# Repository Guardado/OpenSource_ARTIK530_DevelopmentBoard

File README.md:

# OpenSource_ARTIK530_DevelopmentBoard  
An Open Source Development Board for the ARTIK530 SOM  

----

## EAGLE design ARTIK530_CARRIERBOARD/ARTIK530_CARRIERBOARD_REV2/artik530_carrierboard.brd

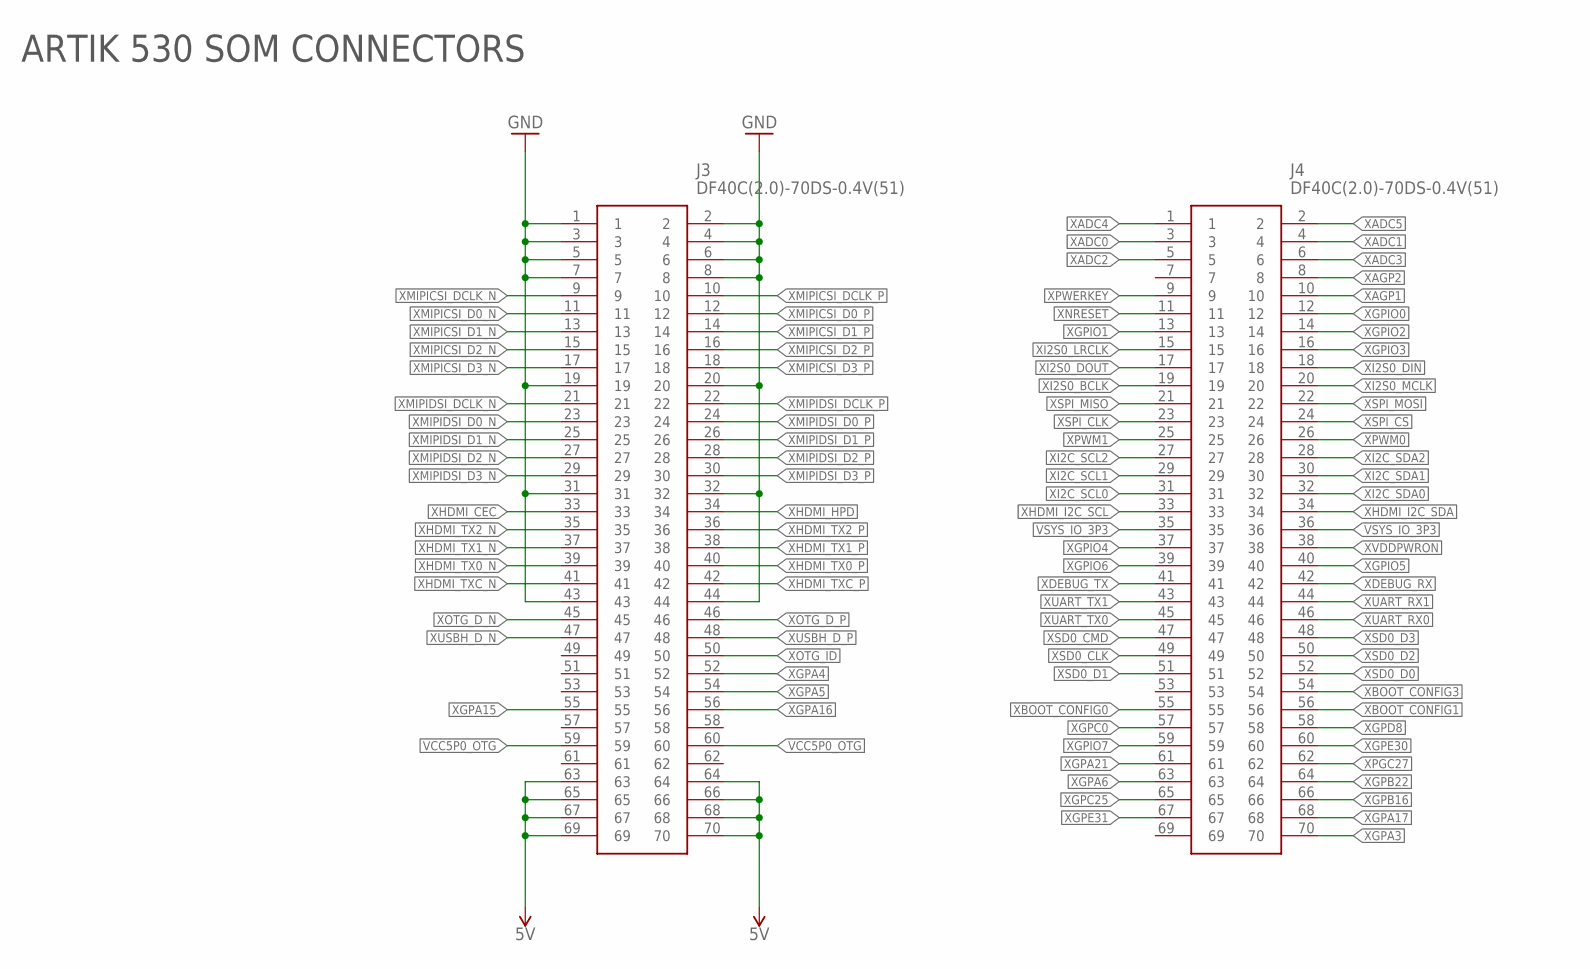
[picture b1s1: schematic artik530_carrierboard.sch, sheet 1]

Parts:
J3, J4: DF40C(2.0)-70DS-0.4V(51)

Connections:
5V: J3.63, J3.64, J3.65, J3.66, J3.67, J3.68, J3.69, J3.70; also elsewhere on the board
GND: J3.1, J3.2, J3.3, J3.4, J3.5, J3.6, J3.7, J3.8, J3.19, J3.20, J3.31, J3.32, J3.43, J3.44; also elsewhere on the board
VCC5P0_OTG: J3.59, J3.60; also elsewhere on the board
VSYS_IO_3P3: J4.35, J4.36; also elsewhere on the board
XADC0: J4.3; also elsewhere on the board
XADC1: J4.4; also elsewhere on the board
XADC2: J4.5; also elsewhere on the board
XADC3: J4.6; also elsewhere on the board
XADC4: J4.1; also elsewhere on the board
XADC5: J4.2; also elsewhere on the board
XAGP1: J4.10
XAGP2: J4.8
XBOOT_CONFIG0: J4.55; also elsewhere on the board
XBOOT_CONFIG1: J4.56; also elsewhere on the board
XBOOT_CONFIG3: J4.54; also elsewhere on the board
XDEBUG_RX: J4.42; also elsewhere on the board
XDEBUG_TX: J4.41; also elsewhere on the board
XGPA3: J4.70
XGPA4: J3.52
XGPA5: J3.54
XGPA6: J4.63
XGPA15: J3.55; also elsewhere on the board
XGPA16: J3.56; also elsewhere on the board
XGPA17: J4.68
XGPA21: J4.61; also elsewhere on the board
XGPB16: J4.66
XGPB22: J4.64
XGPC0: J4.57
XGPC25: J4.65
XGPD8: J4.58; also elsewhere on the board
XGPE30: J4.60
XGPE31: J4.67
XGPIO0: J4.12; also elsewhere on the board
XGPIO1: J4.13; also elsewhere on the board
XGPIO2: J4.14; also elsewhere on the board
XGPIO3: J4.16; also elsewhere on the board
XGPIO4: J4.37; also elsewhere on the board
XGPIO5: J4.40; also elsewhere on the board
XGPIO6: J4.39; also elsewhere on the board
XGPIO7: J4.59; also elsewhere on the board
XHDMI_CEC: J3.33; also elsewhere on the board
XHDMI_HPD: J3.34; also elsewhere on the board
XHDMI_I2C_SCL: J4.33; also elsewhere on the board
XHDMI_I2C_SDA: J4.34; also elsewhere on the board
XHDMI_TX0_N: J3.39; also elsewhere on the board
XHDMI_TX0_P: J3.40; also elsewhere on the board
XHDMI_TX1_N: J3.37; also elsewhere on the board
XHDMI_TX1_P: J3.38; also elsewhere on the board
XHDMI_TX2_N: J3.35; also elsewhere on the board
XHDMI_TX2_P: J3.36; also elsewhere on the board
XHDMI_TXC_N: J3.41; also elsewhere on the board
XHDMI_TXC_P: J3.42; also elsewhere on the board
XI2C_SCL0: J4.31; also elsewhere on the board
XI2C_SCL1: J4.29; also elsewhere on the board
XI2C_SCL2: J4.27; also elsewhere on the board
XI2C_SDA0: J4.32; also elsewhere on the board
XI2C_SDA1: J4.30; also elsewhere on the board
XI2C_SDA2: J4.28; also elsewhere on the board
XI2S0_BCLK: J4.19; also elsewhere on the board
XI2S0_DIN: J4.18; also elsewhere on the board
XI2S0_DOUT: J4.17; also elsewhere on the board
XI2S0_LRCLK: J4.15; also elsewhere on the board
XI2S0_MCLK: J4.20; also elsewhere on the board
XMIPICSI_D0_N: J3.11
XMIPICSI_D0_P: J3.12
XMIPICSI_D1_N: J3.13
XMIPICSI_D1_P: J3.14
XMIPICSI_D2_N: J3.15
XMIPICSI_D2_P: J3.16
XMIPICSI_D3_N: J3.17
XMIPICSI_D3_P: J3.18
XMIPICSI_DCLK_N: J3.9
XMIPICSI_DCLK_P: J3.10
XMIPIDSI_D0_N: J3.23
XMIPIDSI_D0_P: J3.24
XMIPIDSI_D1_N: J3.25
XMIPIDSI_D1_P: J3.26
XMIPIDSI_D2_N: J3.27
XMIPIDSI_D2_P: J3.28
XMIPIDSI_D3_N: J3.29
XMIPIDSI_D3_P: J3.30
XMIPIDSI_DCLK_N: J3.21
XMIPIDSI_DCLK_P: J3.22
XNRESET: J4.11; also elsewhere on the board
XOTG_D_N: J3.45; also elsewhere on the board
XOTG_D_P: J3.46; also elsewhere on the board
XOTG_ID: J3.50; also elsewhere on the board
XPGC27: J4.62
XPWERKEY: J4.9; also elsewhere on the board
XPWM0: J4.26; also elsewhere on the board
XPWM1: J4.25; also elsewhere on the board
XSD0_CLK: J4.49
XSD0_CMD: J4.47
XSD0_D0: J4.52
XSD0_D1: J4.51
XSD0_D2: J4.50
XSD0_D3: J4.48
XSPI_CLK: J4.23; also elsewhere on the board
XSPI_CS: J4.24; also elsewhere on the board
XSPI_MISO: J4.21; also elsewhere on the board
XSPI_MOSI: J4.22; also elsewhere on the board
XUART_RX0: J4.46; also elsewhere on the board
XUART_RX1: J4.44; also elsewhere on the board
XUART_TX0: J4.45; also elsewhere on the board
XUART_TX1: J4.43; also elsewhere on the board
XUSBH_D_N: J3.47; also elsewhere on the board
XUSBH_D_P: J3.48; also elsewhere on the board
XVDDPWRON: J4.38; also elsewhere on the board

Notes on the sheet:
ARTIK 530 SOM CONNECTORS

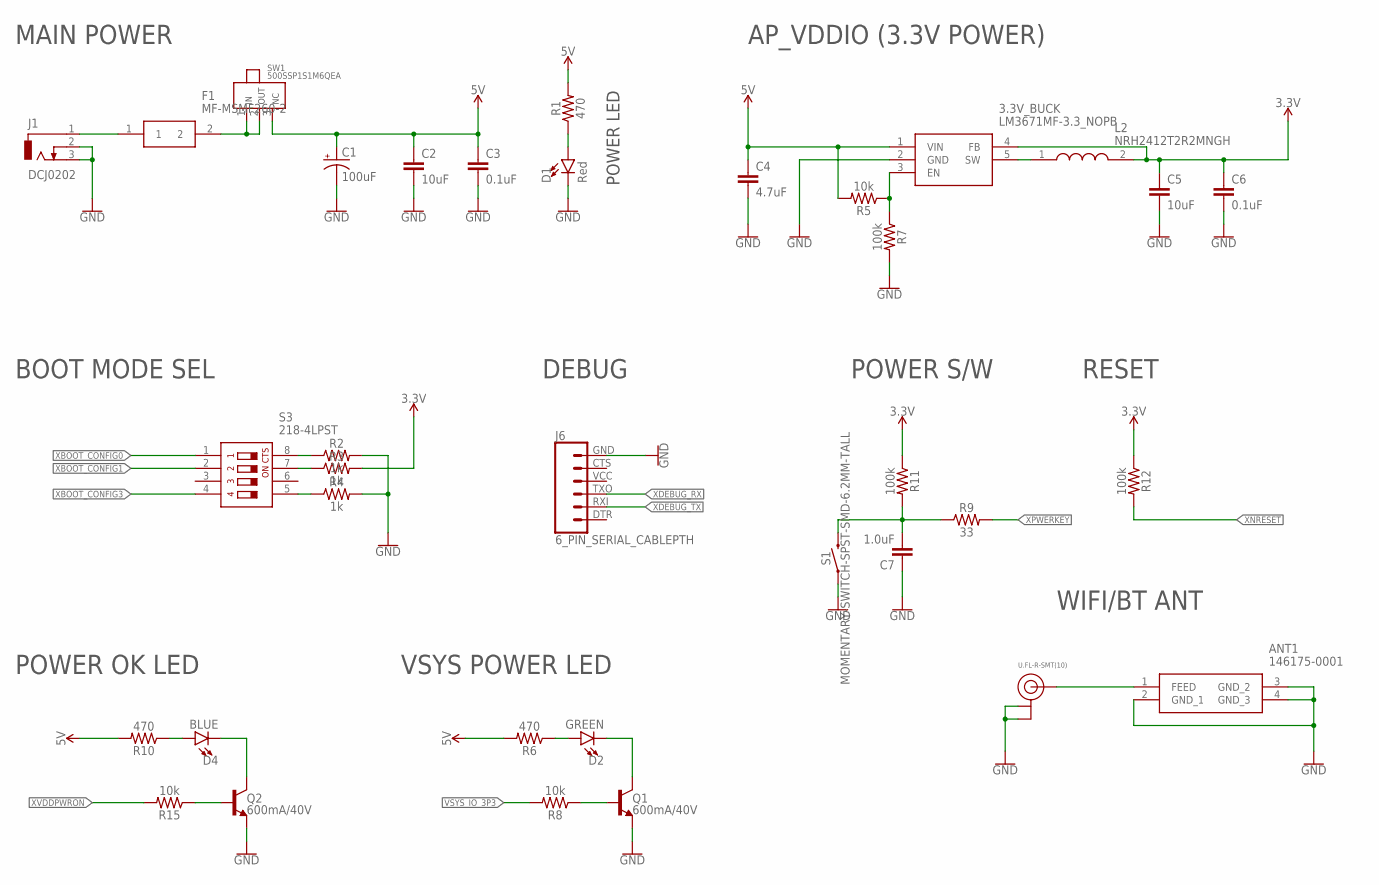
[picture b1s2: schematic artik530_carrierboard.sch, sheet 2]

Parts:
3.3V_BUCK: LM3671MF-3.3_NOPB; SOT95P284X122-5N
ANT1: 146175-0001
C1: 100uF; EIA7343
C2, C5: 10uF; 0603
C3, C6: 0.1uF; 0603
C4: 4.7uF; 0603
C7: 1.0uF; 0603
D1: Red; LED-0603
D2: GREEN; LED-0603
D4: BLUE; LED-0603
F1: MF-MSMF260-2
J1: DCJ0202
J6: 6_PIN_SERIAL_CABLEPTH; FTDI_BASIC
L2: NRH2412T2R2MNGH
Q1, Q2: 600mA/40V; SOT23-3
R1, R6, R10: 470; 0603
R2, R3, R4: 1k; 0603
R5, R8, R15: 10k; 0603
R7, R11, R12: 100k; 0603
R9: 33; 0603
S1: MOMENTARY-SWITCH-SPST-SMD-6.2MM-TALL; TACTILE_SWITCH_SMD_6.2MM_TALL
S3: 218-4LPST; SOIC127P844X265-8N
SW1: 500SSP1S1M6QEA
U$3: U.FL-R-SMT(10)

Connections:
3.3V: 3.3V_BUCK.4 (FB), C5.1, C6.1, L2.2, R3.2, R11.1, R12.1; also elsewhere on the board
5V: 3.3V_BUCK.1 (VIN), C1.A (+), C2.1, C3.1, C4.1, R1.2, R5.2, R6.2, R10.2, SW1.3 (NC); also elsewhere on the board
GND: 3.3V_BUCK.2 (GND), ANT1.2 (GND_1), ANT1.3 (GND_2), ANT1.4 (GND_3), C1.C (-), C2.2, C3.2, C4.2, C5.2, C6.2, C7.1, D1.C, J1.2, J1.3, J6.GND (6), Q1.2 (E), Q2.2 (E), R2.2, R4.2, R7.2, S1.A2 (1), U$3.1 (GND1), U$3.2 (GND2); also elsewhere on the board
unnamed: F1.1, J1.1
unnamed: F1.2, SW1.1 (IN), SW1.2 (OUT)
unnamed: 3.3V_BUCK.5 (SW), L2.1
unnamed: D1.A, R1.1
unnamed: R2.1, S3.8
unnamed: R3.1, S3.7
unnamed: R4.1, S3.5
unnamed: D2.A, R6.1
unnamed: 3.3V_BUCK.3 (EN), R5.1, R7.1
unnamed: D2.C, Q1.3 (C)
unnamed: Q1.1 (B), R8.1
unnamed: C7.2, R9.1, R11.2, S1.B2 (2)
unnamed: D4.A, R10.1
unnamed: D4.C, Q2.3 (C)
unnamed: Q2.1 (B), R15.1
unnamed: ANT1.1 (FEED), U$3.3 (SIG)
VSYS_IO_3P3: R8.2; also elsewhere on the board
XBOOT_CONFIG0: S3.1; also elsewhere on the board
XBOOT_CONFIG1: S3.2; also elsewhere on the board
XBOOT_CONFIG3: S3.4; also elsewhere on the board
XDEBUG_RX: J6.TXO (3); also elsewhere on the board
XDEBUG_TX: J6.RXI (2); also elsewhere on the board
XNRESET: R12.2; also elsewhere on the board
XPWERKEY: R9.2; also elsewhere on the board
XVDDPWRON: R15.2; also elsewhere on the board

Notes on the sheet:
MAIN POWER
POWER LED
BOOT MODE SEL
AP_VDDIO (3.3V POWER)
VSYS POWER LED
POWER S/W
RESET
DEBUG
WIFI/BT ANT
POWER OK LED

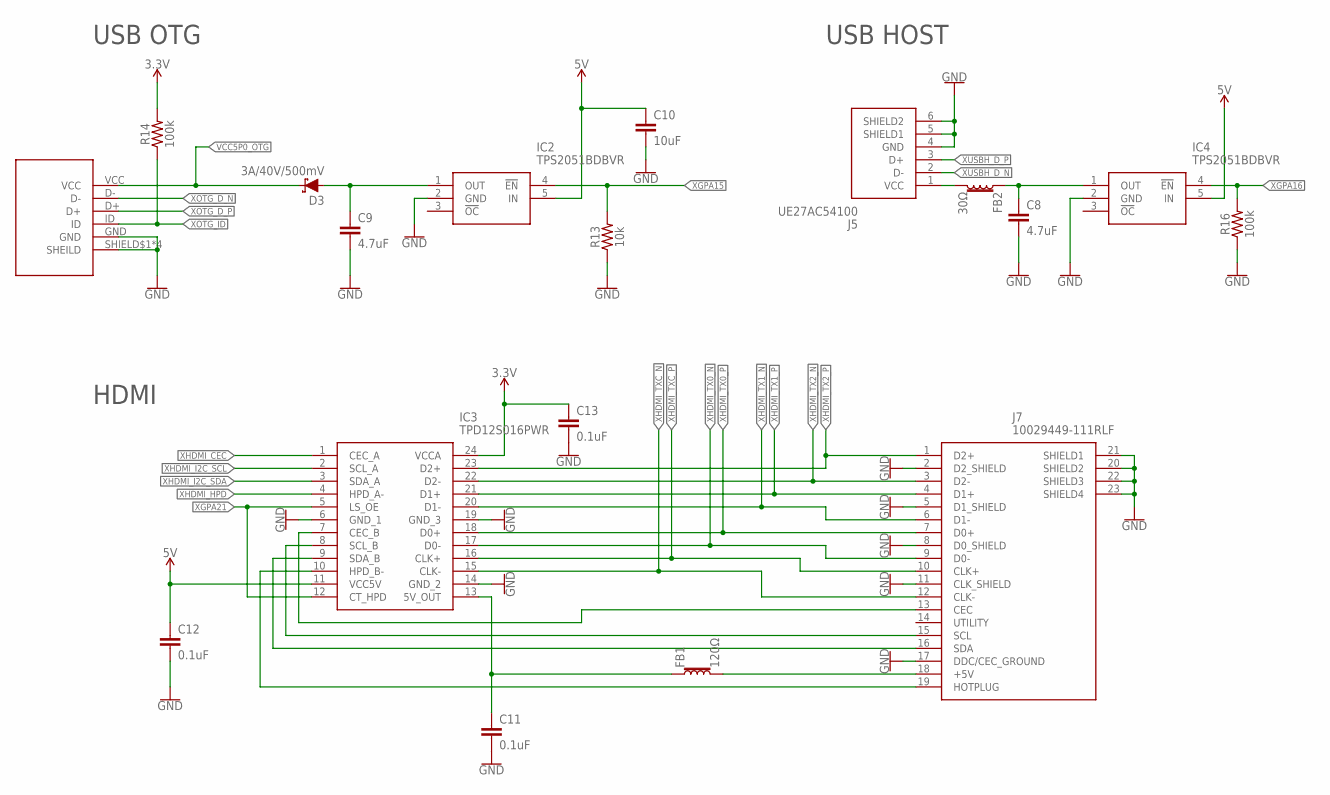
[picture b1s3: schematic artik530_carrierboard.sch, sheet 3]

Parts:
C8, C9: 4.7uF; 0603
C10: 10uF; 0603
C11, C12, C13: 0.1uF; 0603
D3: 3A/40V/500mV; SMA-DIODE
FB1: 120Ω; 0603
FB2: 30Ω; 0603
IC2, IC4: TPS2051BDBVR; SOT95P280X145-5N
IC3: TPD12S016PWR; SOP65P640X120-24N
J2: 10118193-0001LF
J5: UE27AC54100
J7: 10029449-111RLF; 10029449-111RLF_1
R13: 10k; 0603
R14, R16: 100k; 0603

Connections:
3.3V: C13.1, IC3.24 (VCCA), R14.2; also elsewhere on the board
5V: C10.1, C12.1, IC2.5 (IN), IC3.11 (VCC5V), IC4.5 (IN); also elsewhere on the board
GND: C8.2, C9.2, C10.2, C11.2, C12.2, C13.2, IC2.2 (GND), IC3.6 (GND_1), IC3.14 (GND_2), IC3.19 (GND_3), IC4.2 (GND), J2.GND, J2.SHIELD$1 (SHEILD), J2.SHIELD$2 (SHEILD), J2.SHIELD$3 (SHEILD), J2.SHIELD$4 (SHEILD), J5.4 (GND), J5.5 (SHIELD1), J5.6 (SHIELD2), J7.2 (D2_SHIELD), J7.5 (D1_SHIELD), J7.8 (D0_SHIELD), J7.11 (CLK_SHIELD), J7.17 (DDC/CEC_GROUND), J7.20 (SHIELD2), J7.21 (SHIELD1), J7.22 (SHIELD3), J7.23 (SHIELD4), R13.1, R16.1; also elsewhere on the board
unnamed: C11.1, FB1.1, IC3.13 (5V_OUT)
unnamed: C9.1, D3.A, IC2.1 (OUT)
unnamed: IC3.7 (CEC_B), J7.13 (CEC)
unnamed: IC3.8 (SCL_B), J7.15 (SCL)
unnamed: IC3.9 (SDA_B), J7.16 (SDA)
unnamed: IC3.10 (HPD_B-), J7.19 (HOTPLUG)
unnamed: FB1.2, J7.18 (+5V)
unnamed: C8.1, FB2.1, IC4.1 (OUT)
unnamed: FB2.2, J5.1 (VCC)
VCC5P0_OTG: D3.C, J2.VCC; also elsewhere on the board
XGPA15: IC2.4 (!EN), R13.2; also elsewhere on the board
XGPA16: IC4.4 (!EN), R16.2; also elsewhere on the board
XGPA21: IC3.5 (LS_OE), IC3.12 (CT_HPD); also elsewhere on the board
XHDMI_CEC: IC3.1 (CEC_A); also elsewhere on the board
XHDMI_HPD: IC3.4 (HPD_A-); also elsewhere on the board
XHDMI_I2C_SCL: IC3.2 (SCL_A); also elsewhere on the board
XHDMI_I2C_SDA: IC3.3 (SDA_A); also elsewhere on the board
XHDMI_TX0_N: IC3.17 (D0-), J7.9 (D0-); also elsewhere on the board
XHDMI_TX0_P: IC3.18 (D0+), J7.7 (D0+); also elsewhere on the board
XHDMI_TX1_N: IC3.20 (D1-), J7.6 (D1-); also elsewhere on the board
XHDMI_TX1_P: IC3.21 (D1+), J7.4 (D1+); also elsewhere on the board
XHDMI_TX2_N: IC3.22 (D2-), J7.3 (D2-); also elsewhere on the board
XHDMI_TX2_P: IC3.23 (D2+), J7.1 (D2+); also elsewhere on the board
XHDMI_TXC_N: IC3.15 (CLK-), J7.12 (CLK-); also elsewhere on the board
XHDMI_TXC_P: IC3.16 (CLK+), J7.10 (CLK+); also elsewhere on the board
XOTG_D_N: J2.D-; also elsewhere on the board
XOTG_D_P: J2.D+; also elsewhere on the board
XOTG_ID: J2.ID, R14.1; also elsewhere on the board
XUSBH_D_N: J5.2 (D-); also elsewhere on the board
XUSBH_D_P: J5.3 (D+); also elsewhere on the board

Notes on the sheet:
USB OTG
HDMI
USB HOST

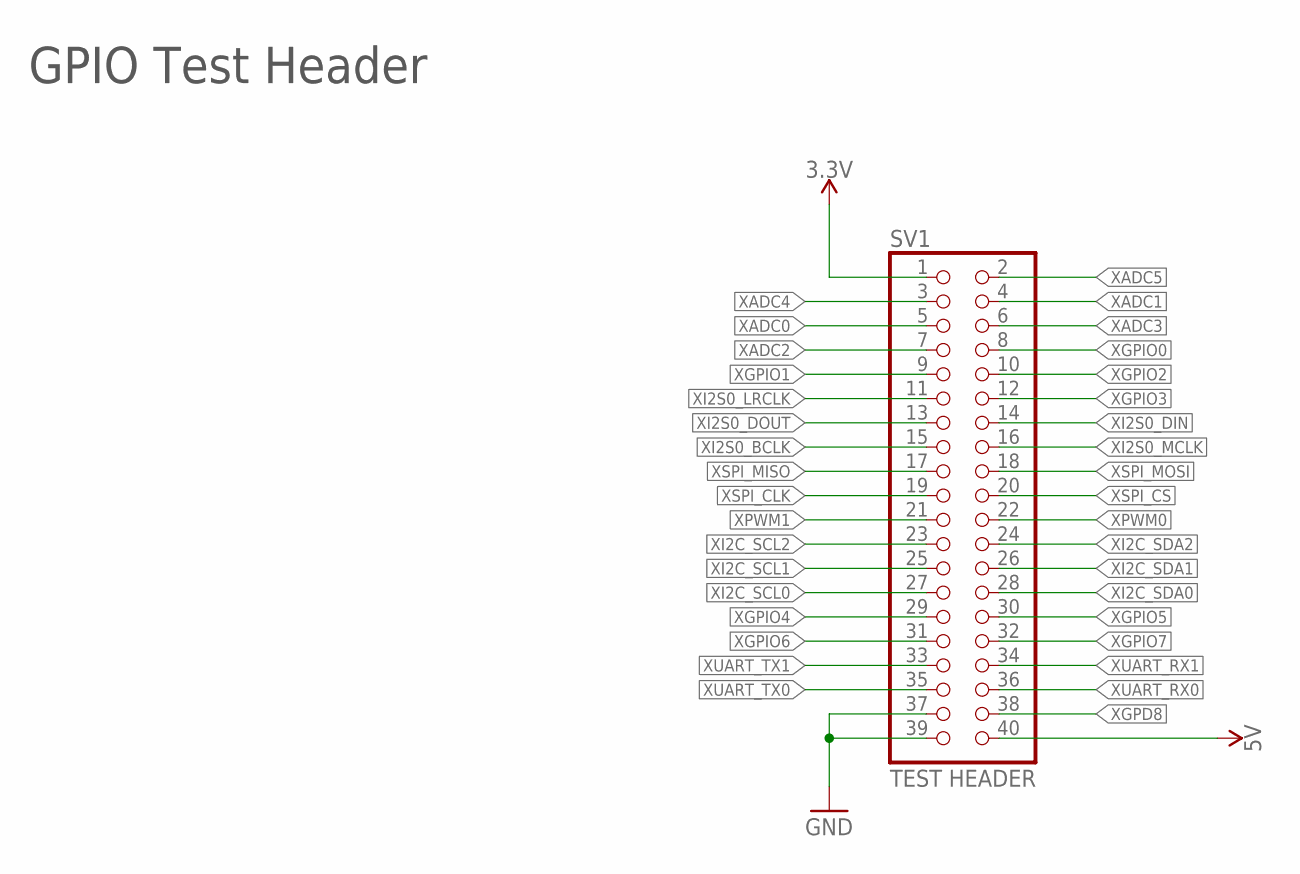
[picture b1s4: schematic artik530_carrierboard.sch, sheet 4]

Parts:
SV1: TEST HEADER; 2X20

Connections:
3.3V: SV1.1; also elsewhere on the board
5V: SV1.40; also elsewhere on the board
GND: SV1.37, SV1.39; also elsewhere on the board
XADC0: SV1.5; also elsewhere on the board
XADC1: SV1.4; also elsewhere on the board
XADC2: SV1.7; also elsewhere on the board
XADC3: SV1.6; also elsewhere on the board
XADC4: SV1.3; also elsewhere on the board
XADC5: SV1.2; also elsewhere on the board
XGPD8: SV1.38; also elsewhere on the board
XGPIO0: SV1.8; also elsewhere on the board
XGPIO1: SV1.9; also elsewhere on the board
XGPIO2: SV1.10; also elsewhere on the board
XGPIO3: SV1.12; also elsewhere on the board
XGPIO4: SV1.29; also elsewhere on the board
XGPIO5: SV1.30; also elsewhere on the board
XGPIO6: SV1.31; also elsewhere on the board
XGPIO7: SV1.32; also elsewhere on the board
XI2C_SCL0: SV1.27; also elsewhere on the board
XI2C_SCL1: SV1.25; also elsewhere on the board
XI2C_SCL2: SV1.23; also elsewhere on the board
XI2C_SDA0: SV1.28; also elsewhere on the board
XI2C_SDA1: SV1.26; also elsewhere on the board
XI2C_SDA2: SV1.24; also elsewhere on the board
XI2S0_BCLK: SV1.15; also elsewhere on the board
XI2S0_DIN: SV1.14; also elsewhere on the board
XI2S0_DOUT: SV1.13; also elsewhere on the board
XI2S0_LRCLK: SV1.11; also elsewhere on the board
XI2S0_MCLK: SV1.16; also elsewhere on the board
XPWM0: SV1.22; also elsewhere on the board
XPWM1: SV1.21; also elsewhere on the board
XSPI_CLK: SV1.19; also elsewhere on the board
XSPI_CS: SV1.20; also elsewhere on the board
XSPI_MISO: SV1.17; also elsewhere on the board
XSPI_MOSI: SV1.18; also elsewhere on the board
XUART_RX0: SV1.36; also elsewhere on the board
XUART_RX1: SV1.34; also elsewhere on the board
XUART_TX0: SV1.35; also elsewhere on the board
XUART_TX1: SV1.33; also elsewhere on the board

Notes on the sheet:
GPIO Test Header

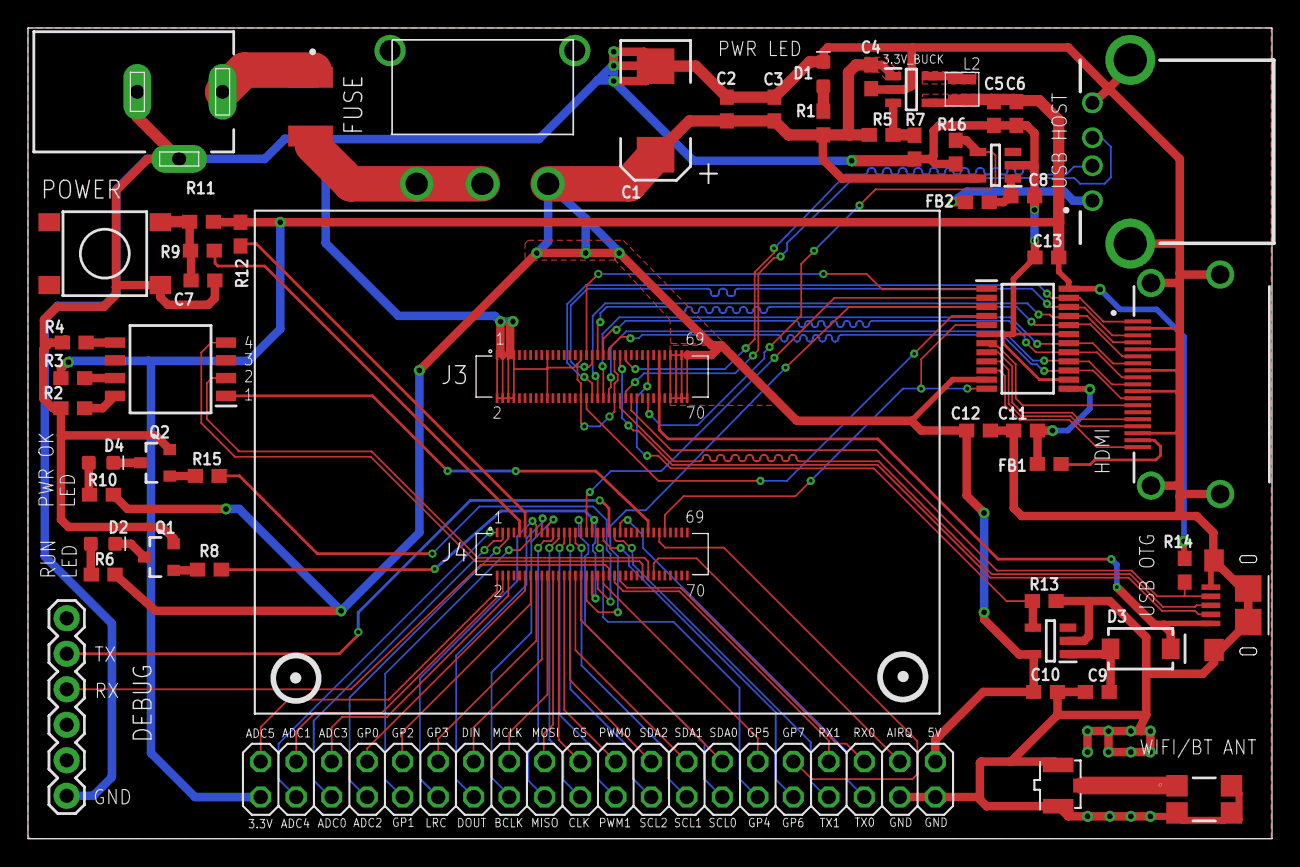
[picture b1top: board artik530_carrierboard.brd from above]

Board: 2 copper layers, 89.0 x 58.0 mm, 56 parts (0 on the bottom side), 94 nets.

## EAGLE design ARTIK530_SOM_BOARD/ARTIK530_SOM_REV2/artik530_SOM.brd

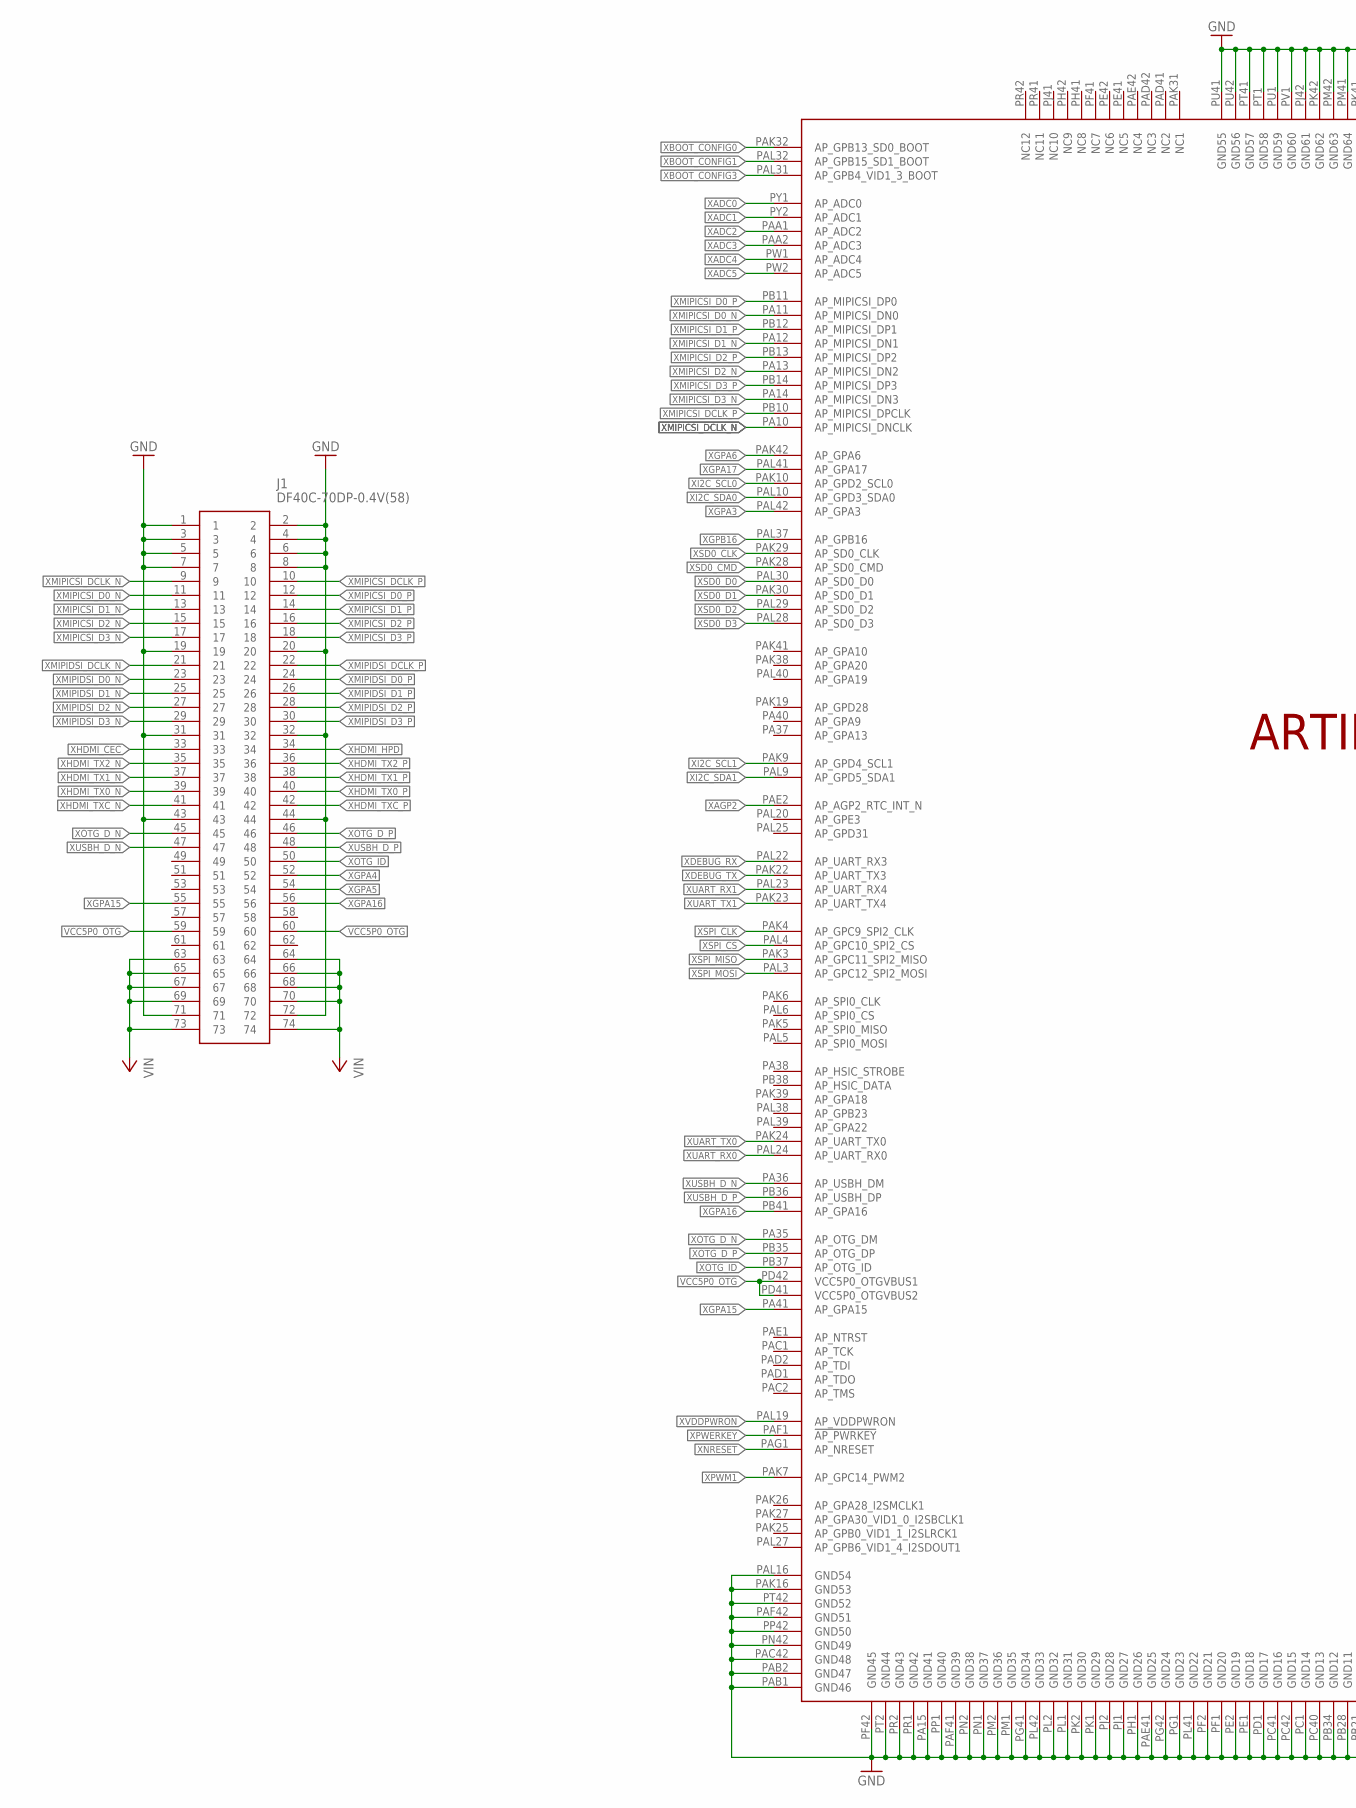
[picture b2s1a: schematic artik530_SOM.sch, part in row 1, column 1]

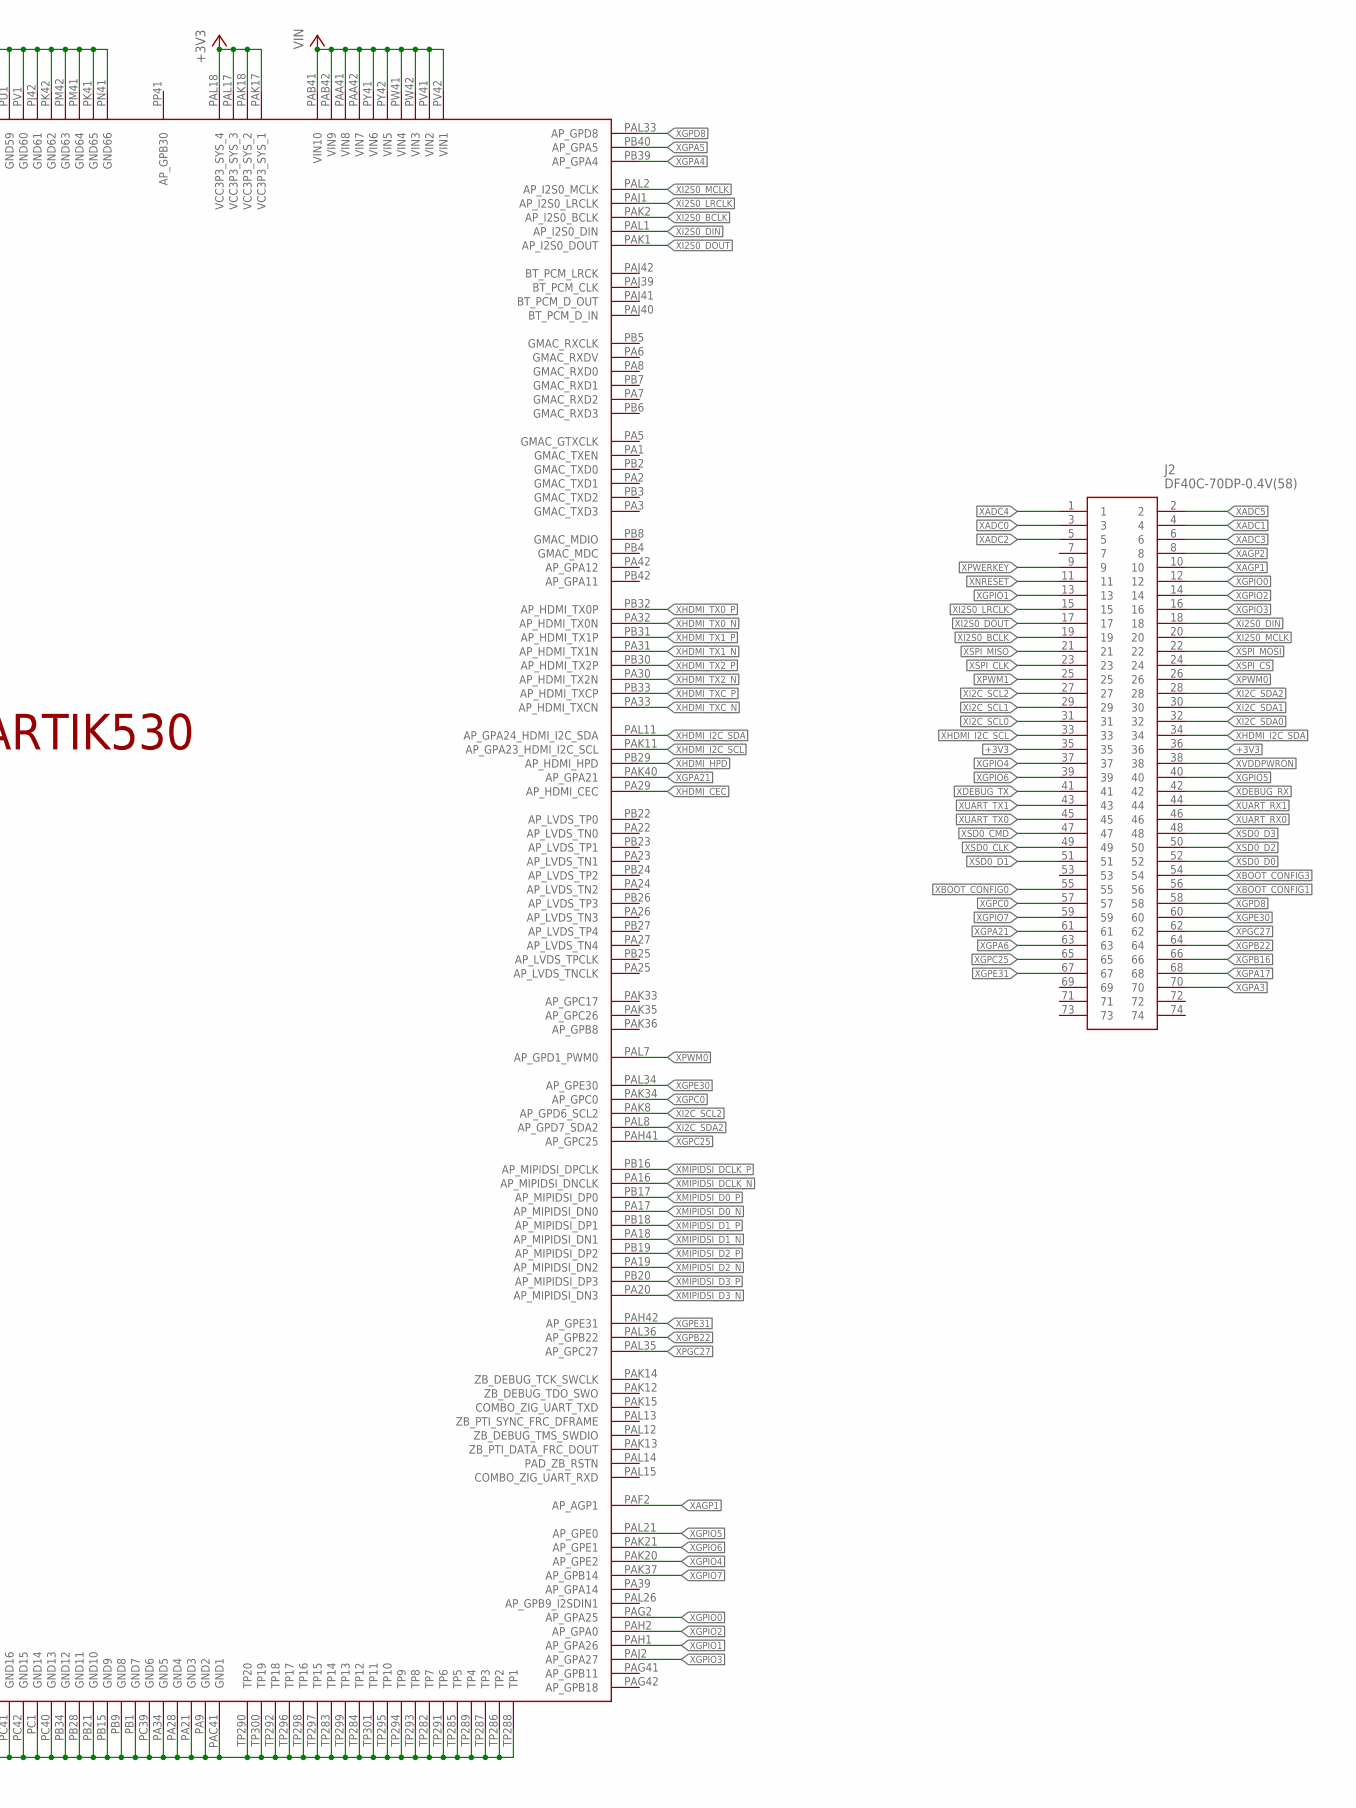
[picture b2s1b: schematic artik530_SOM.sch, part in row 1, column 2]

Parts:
J1, J2: DF40C-70DP-0.4V(58); DF40C70DP04V58
U$1: ARTIK530ARTIK530_SOM; ARTIK5

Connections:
+3V3: J2.35, J2.36, U$1.PAK17 (VCC3P3_SYS_1), U$1.PAK18 (VCC3P3_SYS_2), U$1.PAL17 (VCC3P3_SYS_3), U$1.PAL18 (VCC3P3_SYS_4)
GND: J1.1, J1.2, J1.3, J1.4, J1.5, J1.6, J1.7, J1.8, J1.19, J1.20, J1.31, J1.32, J1.43, J1.44, J1.71, J1.72, U$1.PA9 (GND2), U$1.PA15 (GND41), U$1.PA21 (GND3), U$1.PA28 (GND4), U$1.PA34 (GND5), U$1.PAB1 (GND46), U$1.PAB2 (GND47), U$1.PAC41 (GND1), U$1.PAC42 (GND48), U$1.PAE41 (GND25), U$1.PAF41 (GND39), U$1.PAF42 (GND51), U$1.PAK16 (GND53), U$1.PAL16 (GND54), U$1.PB1 (GND7), U$1.PB9 (GND8), U$1.PB15 (GND9), U$1.PB21 (GND10), U$1.PB28 (GND11), U$1.PB34 (GND12), U$1.PC1 (GND14), U$1.PC39 (GND6), U$1.PC40 (GND13), U$1.PC41 (GND16), U$1.PC42 (GND15), U$1.PD1 (GND17), U$1.PE1 (GND18), U$1.PE2 (GND19), U$1.PF1 (GND20), U$1.PF2 (GND21), U$1.PF42 (GND45), U$1.PG1 (GND23), U$1.PG41 (GND34), U$1.PG42 (GND24), U$1.PH1 (GND26), U$1.PJ1 (GND27), U$1.PJ2 (GND28), U$1.PJ42 (GND61), U$1.PK1 (GND29), U$1.PK2 (GND30), U$1.PK41 (GND65), U$1.PK42 (GND62), U$1.PL1 (GND31), U$1.PL2 (GND32), U$1.PL41 (GND22), U$1.PL42 (GND33), U$1.PM1 (GND35), U$1.PM2 (GND36), U$1.PM41 (GND64), U$1.PM42 (GND63), U$1.PN1 (GND37), U$1.PN2 (GND38), U$1.PN41 (GND66), U$1.PN42 (GND49), U$1.PP1 (GND40), U$1.PP42 (GND50), U$1.PR1 (GND42), U$1.PR2 (GND43), U$1.PT1 (GND58), U$1.PT2 (GND44), U$1.PT41 (GND57), U$1.PT42 (GND52), U$1.PU1 (GND59), U$1.PU41 (GND55), U$1.PU42 (GND56), U$1.PV1 (GND60), U$1.TP282 (TP7), U$1.TP283 (TP14), U$1.TP284 (TP12), U$1.TP285 (TP5), U$1.TP286 (TP2), U$1.TP287 (TP3), U$1.TP288 (TP1), U$1.TP289 (TP4), U$1.TP290 (TP20), U$1.TP291 (TP6), U$1.TP292 (TP18), U$1.TP293 (TP8), U$1.TP294 (TP9), U$1.TP295 (TP10), U$1.TP296 (TP17), U$1.TP297 (TP15), U$1.TP298 (TP16), U$1.TP299 (TP13), U$1.TP300 (TP19), U$1.TP301 (TP11)
VCC: J1.63, J1.64, J1.65, J1.66, J1.67, J1.68, J1.69, J1.70, J1.73, J1.74, U$1.PAA41 (VIN8), U$1.PAA42 (VIN7), U$1.PAB41 (VIN10), U$1.PAB42 (VIN9), U$1.PV41 (VIN2), U$1.PV42 (VIN1), U$1.PW41 (VIN4), U$1.PW42 (VIN3), U$1.PY41 (VIN6), U$1.PY42 (VIN5)
VCC5P0_OTG: J1.59, J1.60, U$1.PD41 (VCC5P0_OTGVBUS2), U$1.PD42 (VCC5P0_OTGVBUS1)
XADC0: J2.3, U$1.PY1 (AP_ADC0)
XADC1: J2.4, U$1.PY2 (AP_ADC1)
XADC2: J2.5, U$1.PAA1 (AP_ADC2)
XADC3: J2.6, U$1.PAA2 (AP_ADC3)
XADC4: J2.1, U$1.PW1 (AP_ADC4)
XADC5: J2.2, U$1.PW2 (AP_ADC5)
XAGP1: J2.10, U$1.PAF2 (AP_AGP1)
XAGP2: J2.8, U$1.PAE2 (AP_AGP2_RTC_INT_N)
XBOOT_CONFIG0: J2.55, U$1.PAK32 (AP_GPB13_SD0_BOOT)
XBOOT_CONFIG1: J2.56, U$1.PAL32 (AP_GPB15_SD1_BOOT)
XBOOT_CONFIG3: J2.54, U$1.PAL31 (AP_GPB4_VID1_3_BOOT)
XDEBUG_RX: J2.42, U$1.PAL22 (AP_UART_RX3)
XDEBUG_TX: J2.41, U$1.PAK22 (AP_UART_TX3)
XGPA3: J2.70, U$1.PAL42 (AP_GPA3)
XGPA4: J1.52, U$1.PB39 (AP_GPA4)
XGPA5: J1.54, U$1.PB40 (AP_GPA5)
XGPA6: J2.63, U$1.PAK42 (AP_GPA6)
XGPA15: J1.55, U$1.PA41 (AP_GPA15)
XGPA16: J1.56, U$1.PB41 (AP_GPA16)
XGPA17: J2.68, U$1.PAL41 (AP_GPA17)
XGPA21: J2.61, U$1.PAK40 (AP_GPA21)
XGPB16: J2.66, U$1.PAL37 (AP_GPB16)
XGPB22: J2.64, U$1.PAL36 (AP_GPB22)
XGPC0: J2.57, U$1.PAK34 (AP_GPC0)
XGPC25: J2.65, U$1.PAH41 (AP_GPC25)
XGPD8: J2.58, U$1.PAL33 (AP_GPD8)
XGPE30: J2.60, U$1.PAL34 (AP_GPE30)
XGPE31: J2.67, U$1.PAH42 (AP_GPE31)
XGPIO0: J2.12, U$1.PAG2 (AP_GPA25)
XGPIO1: J2.13, U$1.PAH1 (AP_GPA26)
XGPIO2: J2.14, U$1.PAH2 (AP_GPA0)
XGPIO3: J2.16, U$1.PAJ2 (AP_GPA27)
XGPIO4: J2.37, U$1.PAK20 (AP_GPE2)
XGPIO5: J2.40, U$1.PAL21 (AP_GPE0)
XGPIO6: J2.39, U$1.PAK21 (AP_GPE1)
XGPIO7: J2.59, U$1.PAK37 (AP_GPB14)
XHDMI_CEC: J1.33, U$1.PA29 (AP_HDMI_CEC)
XHDMI_HPD: J1.34, U$1.PB29 (AP_HDMI_HPD)
XHDMI_I2C_SCL: J2.33, U$1.PAK11 (AP_GPA23_HDMI_I2C_SCL)
XHDMI_I2C_SDA: J2.34, U$1.PAL11 (AP_GPA24_HDMI_I2C_SDA)
XHDMI_TX0_N: J1.39, U$1.PA32 (AP_HDMI_TX0N)
XHDMI_TX0_P: J1.40, U$1.PB32 (AP_HDMI_TX0P)
XHDMI_TX1_N: J1.37, U$1.PA31 (AP_HDMI_TX1N)
XHDMI_TX1_P: J1.38, U$1.PB31 (AP_HDMI_TX1P)
XHDMI_TX2_N: J1.35, U$1.PA30 (AP_HDMI_TX2N)
XHDMI_TX2_P: J1.36, U$1.PB30 (AP_HDMI_TX2P)
XHDMI_TXC_N: J1.41, U$1.PA33 (AP_HDMI_TXCN)
XHDMI_TXC_P: J1.42, U$1.PB33 (AP_HDMI_TXCP)
XI2C_SCL0: J2.31, U$1.PAK10 (AP_GPD2_SCL0)
XI2C_SCL1: J2.29, U$1.PAK9 (AP_GPD4_SCL1)
XI2C_SCL2: J2.27, U$1.PAK8 (AP_GPD6_SCL2)
XI2C_SDA0: J2.32, U$1.PAL10 (AP_GPD3_SDA0)
XI2C_SDA1: J2.30, U$1.PAL9 (AP_GPD5_SDA1)
XI2C_SDA2: J2.28, U$1.PAL8 (AP_GPD7_SDA2)
XI2S0_BCLK: J2.19, U$1.PAK2 (AP_I2S0_BCLK)
XI2S0_DIN: J2.18, U$1.PAL1 (AP_I2S0_DIN)
XI2S0_DOUT: J2.17, U$1.PAK1 (AP_I2S0_DOUT)
XI2S0_LRCLK: J2.15, U$1.PAJ1 (AP_I2S0_LRCLK)
XI2S0_MCLK: J2.20, U$1.PAL2 (AP_I2S0_MCLK)
XMIPICSI_D0_N: J1.11, U$1.PA11 (AP_MIPICSI_DN0)
XMIPICSI_D0_P: J1.12, U$1.PB11 (AP_MIPICSI_DP0)
XMIPICSI_D1_N: J1.13, U$1.PA12 (AP_MIPICSI_DN1)
XMIPICSI_D1_P: J1.14, U$1.PB12 (AP_MIPICSI_DP1)
XMIPICSI_D2_N: J1.15, U$1.PA13 (AP_MIPICSI_DN2)
XMIPICSI_D2_P: J1.16, U$1.PB13 (AP_MIPICSI_DP2)
XMIPICSI_D3_N: J1.17, U$1.PA14 (AP_MIPICSI_DN3)
XMIPICSI_D3_P: J1.18, U$1.PB14 (AP_MIPICSI_DP3)
XMIPICSI_DCLK_N: J1.9, U$1.PA10 (AP_MIPICSI_DNCLK)
XMIPICSI_DCLK_P: J1.10, U$1.PB10 (AP_MIPICSI_DPCLK)
XMIPIDSI_D0_N: J1.23, U$1.PA17 (AP_MIPIDSI_DN0)
XMIPIDSI_D0_P: J1.24, U$1.PB17 (AP_MIPIDSI_DP0)
XMIPIDSI_D1_N: J1.25, U$1.PA18 (AP_MIPIDSI_DN1)
XMIPIDSI_D1_P: J1.26, U$1.PB18 (AP_MIPIDSI_DP1)
XMIPIDSI_D2_N: J1.27, U$1.PA19 (AP_MIPIDSI_DN2)
XMIPIDSI_D2_P: J1.28, U$1.PB19 (AP_MIPIDSI_DP2)
XMIPIDSI_D3_N: J1.29, U$1.PA20 (AP_MIPIDSI_DN3)
XMIPIDSI_D3_P: J1.30, U$1.PB20 (AP_MIPIDSI_DP3)
XMIPIDSI_DCLK_N: J1.21, U$1.PA16 (AP_MIPIDSI_DNCLK)
XMIPIDSI_DCLK_P: J1.22, U$1.PB16 (AP_MIPIDSI_DPCLK)
XNRESET: J2.11, U$1.PAG1 (AP_NRESET)
XOTG_D_N: J1.45, U$1.PA35 (AP_OTG_DM)
XOTG_D_P: J1.46, U$1.PB35 (AP_OTG_DP)
XOTG_ID: J1.50, U$1.PB37 (AP_OTG_ID)
XPGC27: J2.62, U$1.PAL35 (AP_GPC27)
XPWERKEY: J2.9, U$1.PAF1 (!AP_PWRKEY)
XPWM0: J2.26, U$1.PAL7 (AP_GPD1_PWM0)
XPWM1: J2.25, U$1.PAK7 (AP_GPC14_PWM2)
XSD0_CLK: J2.49, U$1.PAK29 (AP_SD0_CLK)
XSD0_CMD: J2.47, U$1.PAK28 (AP_SD0_CMD)
XSD0_D0: J2.52, U$1.PAL30 (AP_SD0_D0)
XSD0_D1: J2.51, U$1.PAK30 (AP_SD0_D1)
XSD0_D2: J2.50, U$1.PAL29 (AP_SD0_D2)
XSD0_D3: J2.48, U$1.PAL28 (AP_SD0_D3)
XSPI_CLK: J2.23, U$1.PAK4 (AP_GPC9_SPI2_CLK)
XSPI_CS: J2.24, U$1.PAL4 (AP_GPC10_SPI2_CS)
XSPI_MISO: J2.21, U$1.PAK3 (AP_GPC11_SPI2_MISO)
XSPI_MOSI: J2.22, U$1.PAL3 (AP_GPC12_SPI2_MOSI)
XUART_RX0: J2.46, U$1.PAL24 (AP_UART_RX0)
XUART_RX1: J2.44, U$1.PAL23 (AP_UART_RX4)
XUART_TX0: J2.45, U$1.PAK24 (AP_UART_TX0)
XUART_TX1: J2.43, U$1.PAK23 (AP_UART_TX4)
XUSBH_D_N: J1.47, U$1.PA36 (AP_USBH_DM)
XUSBH_D_P: J1.48, U$1.PB36 (AP_USBH_DP)
XVDDPWRON: J2.38, U$1.PAL19 (AP_VDDPWRON)

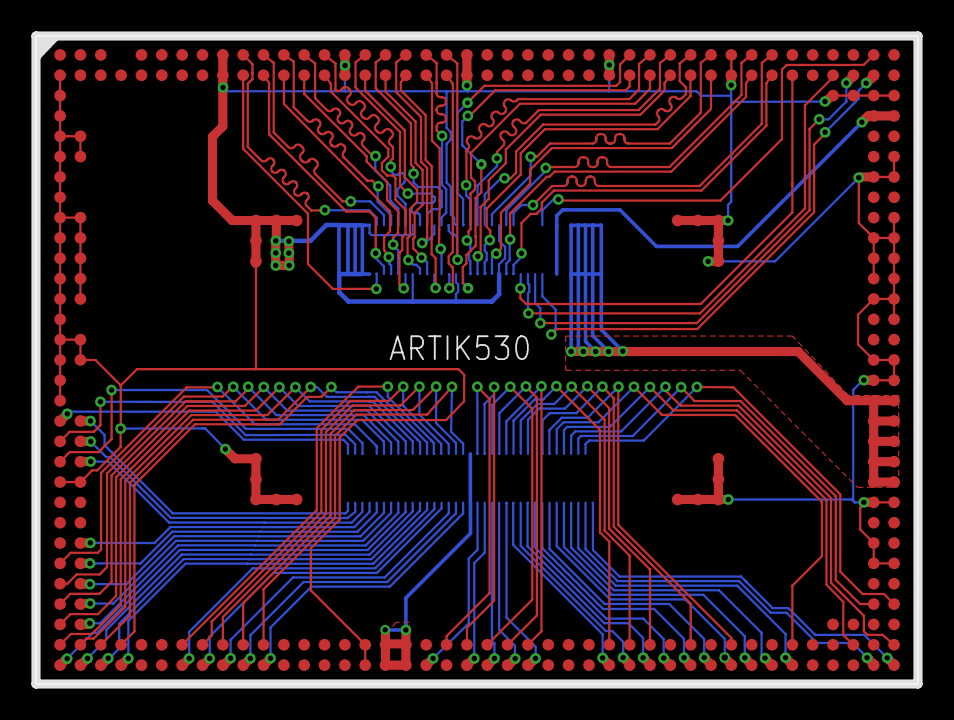
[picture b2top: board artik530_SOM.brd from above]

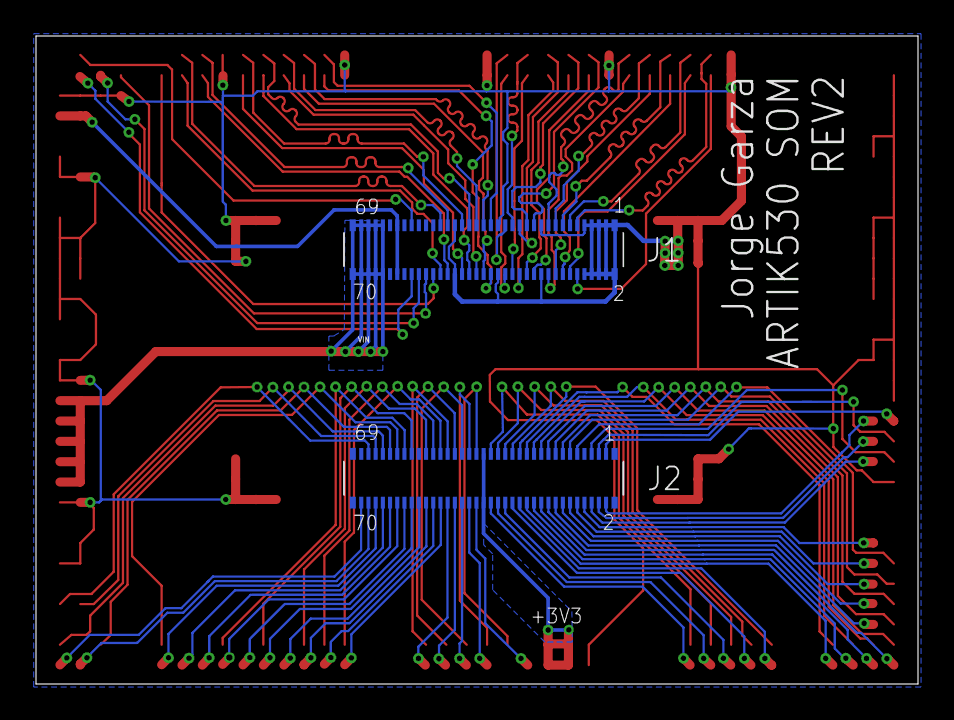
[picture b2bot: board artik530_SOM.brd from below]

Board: 2 copper layers, 49.0 x 36.0 mm, 3 parts (2 on the bottom side), 108 nets.

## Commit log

2019-03-06 ARTIK530 CarrierBoard and SOM commit
    Commit of the Artik and Carrier Board up to REV3
2019-03-06 Added Pictures

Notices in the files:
parts and their libraries:
SparkFun-Aesthetics: Licensing: Creative Commons ShareAlike 4.0 International - https://creativecommons.org/licenses/by-sa/4.0
